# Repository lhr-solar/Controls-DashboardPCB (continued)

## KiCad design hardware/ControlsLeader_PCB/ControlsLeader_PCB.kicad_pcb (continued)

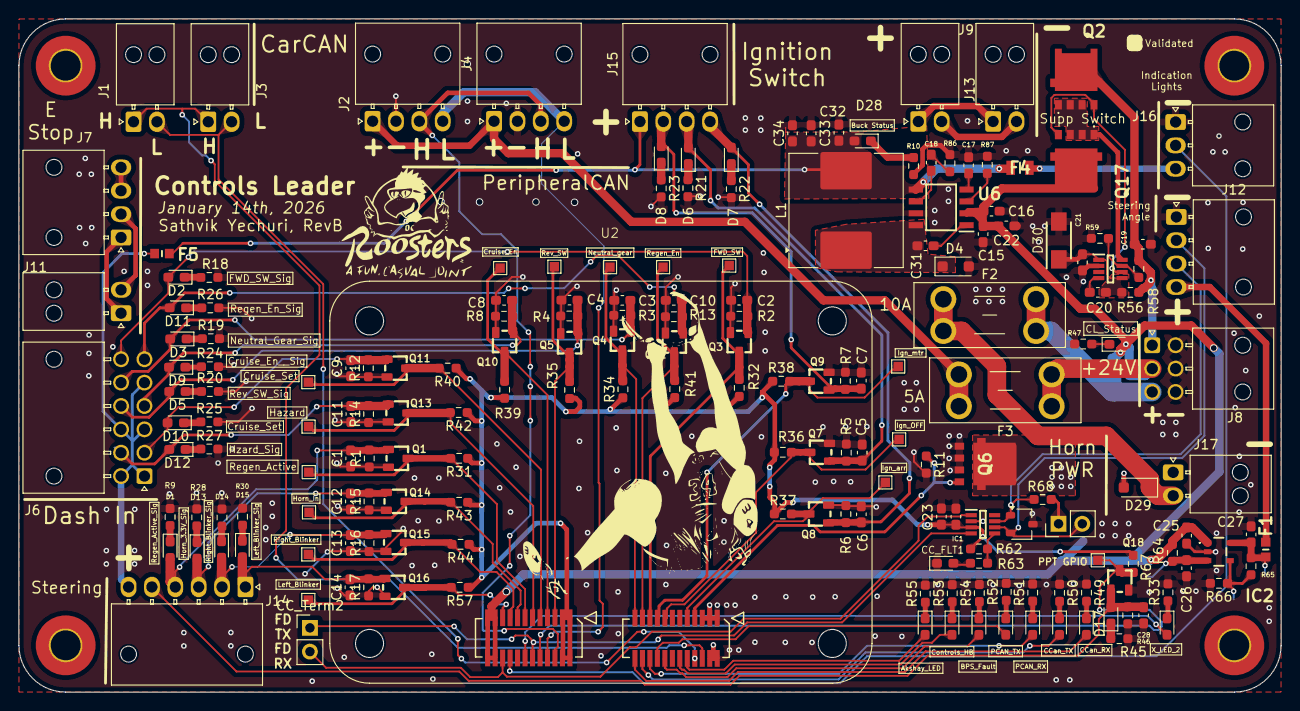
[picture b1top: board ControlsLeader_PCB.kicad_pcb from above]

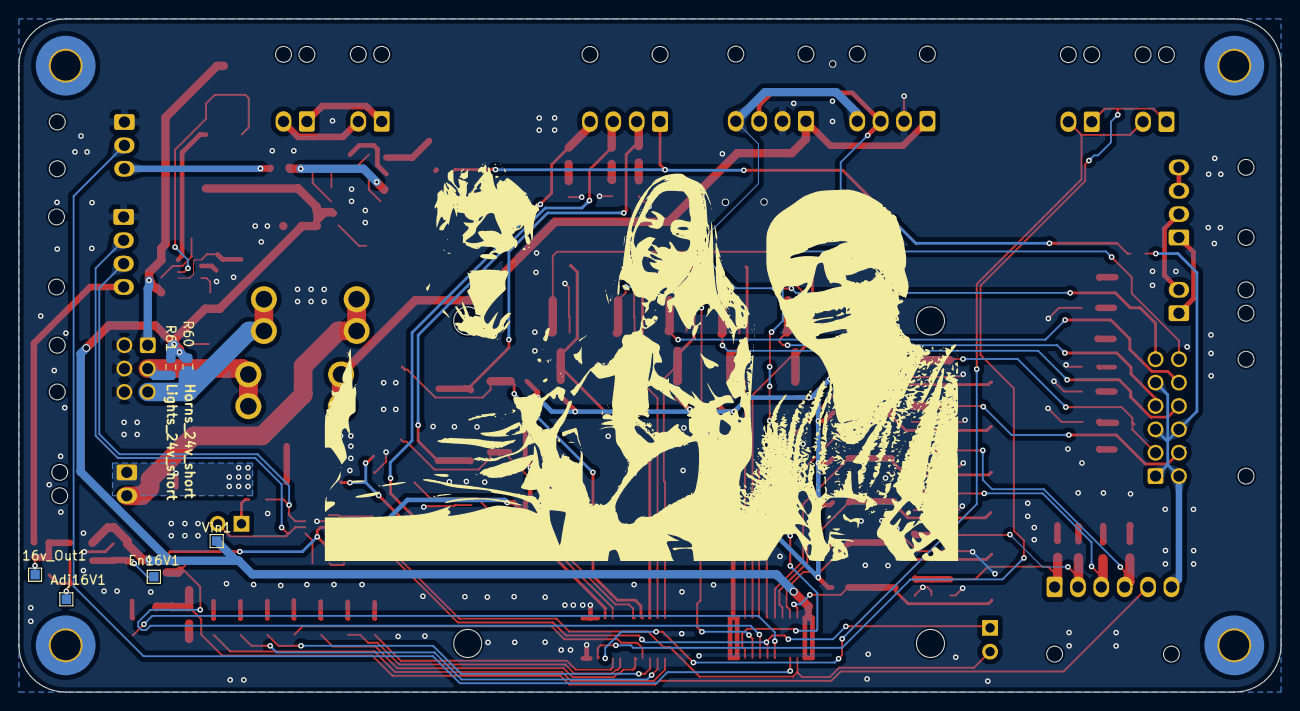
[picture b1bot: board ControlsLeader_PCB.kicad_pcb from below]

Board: 2 copper layers, 135.0 x 72.0 mm, 200 parts (6 on the bottom side), 108 nets.

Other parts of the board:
16v_Out1: 5V_Out; TestPoint_Pad_1.0x1.0mm
Adj16V1: Adj5V; TestPoint_Pad_1.0x1.0mm
C15, C32, C33, C34: 10uF; C_0603_1608Metric_Pad1.08x0.95mm_HandSolder
C16: 1uF; C_0603_1608Metric_Pad1.08x0.95mm_HandSolder
C17: 10nF; C_0603_1608Metric_Pad1.08x0.95mm_HandSolder
C18: 3.3nF; C_0603_1608Metric_Pad1.08x0.95mm_HandSolder
C31: 0.1uF; C_0603_1608Metric_Pad1.08x0.95mm_HandSolder
D4: MBR230S1F; D_SOD-123F
En16V1: Enable5V; TestPoint_Pad_1.0x1.0mm
L1: 100uH; L_Coilcraft_MSS1246-XXX
R86: 16k; R_0603_1608Metric_Pad0.98x0.95mm_HandSolder
R87: ROSC; R_0603_1608Metric_Pad0.98x0.95mm_HandSolder
U6: TPS5405DR

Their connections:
+24V: C15.1, C16.1, U6.2 (VIN); also elsewhere on the board
/5V_Buck: C32.1, C33.1, C34.1, L1.2, U6.5 (VSENSE); also elsewhere on the board
/24v_5v_Buck/LX: C31.2, D4.1 (K), L1.1, U6.8 (LX)
/24v_5v_Buck/ROSC: R87.1, U6.3 (ROSC)
/Steering Angle Sensor Components/24v to 16v ldo/16v_prefuse: 16v_Out1.1; also elsewhere on the board
GND: C15.2, C16.2, C17.2, C32.2, C33.2, C34.2, D4.2 (A), R86.2, R87.2, U6.7 (GND); also elsewhere on the board
unnamed: C18.2, R86.1
unnamed 100: Adj16V1.1; also elsewhere on the board
unnamed 101: En16V1.1; also elsewhere on the board
unnamed: C31.1, U6.1 (BOOT)
unnamed: C18.1, U6.6 (COMP)
unnamed: C17.1, U6.4 (SS)

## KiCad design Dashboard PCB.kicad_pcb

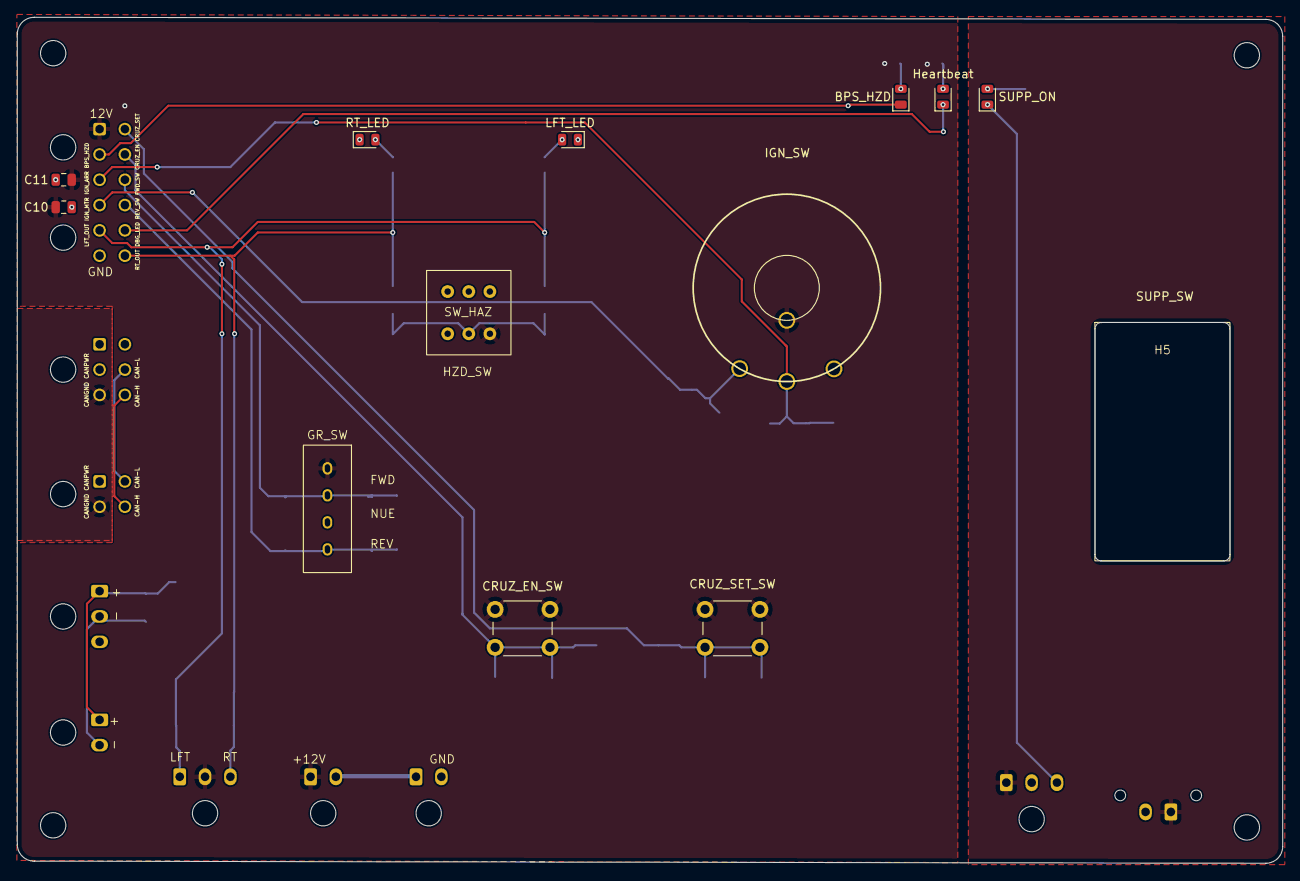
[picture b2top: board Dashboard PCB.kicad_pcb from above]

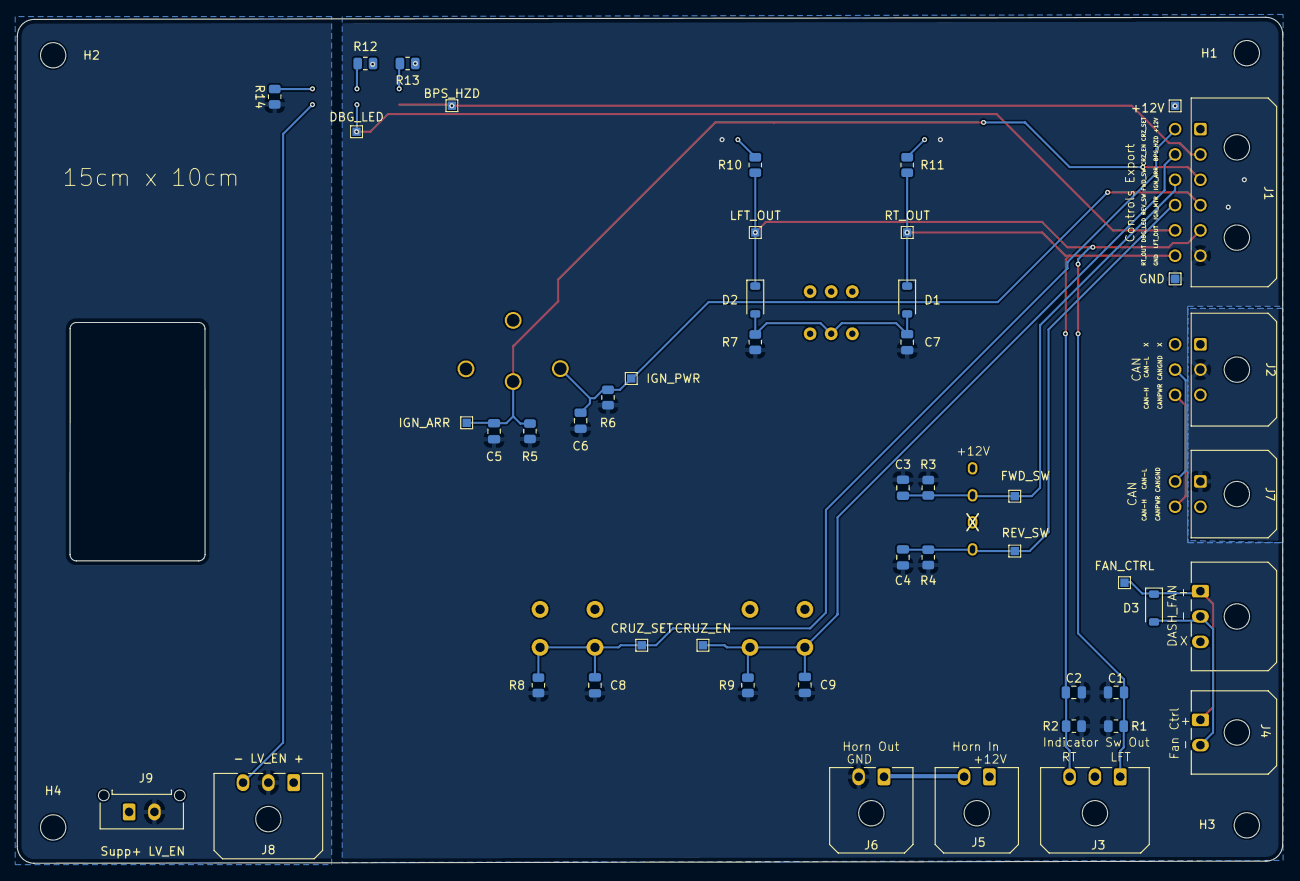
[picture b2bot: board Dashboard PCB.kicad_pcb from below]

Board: 2 copper layers, 150.0 x 100.2 mm, 66 parts (49 on the bottom side), 28 nets.

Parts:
+12V: TestPoint; TestPoint_Pad_1.0x1.0mm
BPS_HZD: SMD_0805_RED; LED_0805_2012Metric
BPS_HZD#2: TestPoint; TestPoint_Pad_1.0x1.0mm
C1, C2, C3, C4, C5, C6, C7, C8, C9: 5uF; C_0805_2012Metric
C10, C11: 100uF; C_0805_2012Metric
CRUZ_EN: TestPoint; TestPoint_Pad_1.0x1.0mm
CRUZ_EN_SW: CRUSE_EN_SW_12V; SW_PUSH_6mm
CRUZ_SET: TestPoint; TestPoint_Pad_1.0x1.0mm
CRUZ_SET_SW: CRUSE_SET_SW_12V; SW_PUSH_6mm
D1, D2: BAV16W; D_SOD-123
D3: 1N5819HW; D_SOD-123
DASH_FAN1: DASHBOARD_FAN_12V; Molex_Micro-Fit_3.0_43650-0300_1x03_P3.00mm_Horizontal
DBG_LED: TestPoint; TestPoint_Pad_1.0x1.0mm
FAN_CTRL: TestPoint; TestPoint_Pad_1.0x1.0mm
FWD_SW: TestPoint; TestPoint_Pad_1.0x1.0mm
GND: TestPoint; TestPoint_Pad_1.0x1.0mm
GR_SW: GEAR_SW_12V; 3posSlideToggle
H1, H2, H3, H4: MountingHole; MountingHole_3mm
H5: SuppSwitchMount; Supp_Switch
HZD_SW: HAZARD_SWITCH_12V; Toggle
Heartbeat: SMD_0805_GRN; LED_0805_2012Metric
IGN_ARR: TestPoint; TestPoint_Pad_1.0x1.0mm
IGN_PWR: TestPoint; TestPoint_Pad_1.0x1.0mm
IGN_SW1: IGNITION_SW_12V; SW_3POS_ROT
J1: Controls_Leader_Export_02x06; Molex_Micro-Fit_3.0_43045-1200_2x06_P3.00mm_Horizontal
J2: Conn_02x03_CAN; Molex_Micro-Fit_3.0_43045-0600_2x03_P3.00mm_Horizontal
J3: INDICATOR_SWITCH_OUT; Molex_Micro-Fit_3.0_43650-0300_1x03_P3.00mm_Horizontal
J4: FAN_CTRL_01x02; Molex_Micro-Fit_3.0_43650-0200_1x02_P3.00mm_Horizontal
J5: Horn_In_01x02; Molex_Micro-Fit_3.0_43650-0200_1x02_P3.00mm_Horizontal
J6: Horn_Out_01x02; Molex_Micro-Fit_3.0_43650-0200_1x02_P3.00mm_Horizontal
J7: Conn_02x03_CAN; Molex_Micro-Fit_3.0_43045-0400_2x02_P3.00mm_Horizontal
J8: Supp_Out; Molex_Micro-Fit_3.0_43650-0300_1x03_P3.00mm_Horizontal
J9: Supp_In; Molex_Micro-Fit_3.0_43650-0215_1x02_P3.00mm_Vertical
LFT_LED: SMD_0805; LED_0805_2012Metric
LFT_OUT: TestPoint; TestPoint_Pad_1.0x1.0mm
R1, R2, R3, R4, R5, R6, R7, R8, R9: 10k; R_0805_2012Metric
R10, R11, R12, R14: 5.1k; R_0805_2012Metric
R13: HZD_RES_VAL; R_0805_2012Metric
REV_SW: TestPoint; TestPoint_Pad_1.0x1.0mm
RT_LED: SMD_0805; LED_0805_2012Metric
RT_OUT: TestPoint; TestPoint_Pad_1.0x1.0mm
SUPP_ON: LED; LED_0805_2012Metric

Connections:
+12V: +12V.1, C10.1, C11.1, CRUZ_EN_SW.1, CRUZ_SET_SW.1, GR_SW.1, HZD_SW.1, IGN_SW1.1, J1.1, J3.2, J5.1, R12.1, R13.1
/BPS_HZD: BPS_HZD.1 (K), BPS_HZD#2.1, J1.2
/CAN+12V: J2.3, J7.2
/CAN-H: J2.6, J7.4
/CAN-L: J2.5, J7.3
/CANGND: J2.2, J7.1
/CRUZ_EN: C9.1, CRUZ_EN.1, CRUZ_EN_SW.2, J1.8, R9.2
/CRUZ_SET: C8.1, CRUZ_SET.1, CRUZ_SET_SW.2, J1.7, R8.1
/DBG_LED: DBG_LED.1, Heartbeat.1 (K), J1.11
/FAN+: D3.1 (K), DASH_FAN1.1, FAN_CTRL.1, J4.1
/FAN-: D3.2 (A), DASH_FAN1.2, J4.2
/FWD_SW: C3.2, FWD_SW.1, GR_SW.2, J1.9, R3.2
/IGN_ARR: C5.1, IGN_ARR.1, IGN_SW1.3, J1.3, R5.2
/IGN_MTR: C6.1, IGN_PWR.1, IGN_SW1.2, J1.4, R6.2
/LFT_OUT: C1.2, D2.1 (K), J1.5, J3.1, LFT_OUT.1, R1.1, R10.1
/LV_EN: J8.2, J9.2, R14.1
/REV_SW: C4.1, GR_SW.4, J1.10, R4.1, REV_SW.1
/RT_OUT: C2.1, D1.1 (K), J1.12, J3.3, R2.2, R11.1, RT_OUT.1
/Supp+: J8.1, J9.1
/Supp-: J8.3, SUPP_ON.1 (K)
GND: C1.1, C2.2, C3.1, C4.2, C5.2, C6.2, C7.2, C8.2, C9.2, C10.2, C11.2, GND.1, J1.6, J6.2, LFT_LED.1 (K), R1.2, R2.1, R3.1, R4.2, R5.1, R6.1, R7.1, R8.2, R9.1, RT_LED.1 (K)
unnamed: BPS_HZD.2 (A), R13.2
unnamed: C7.1, D1.2 (A), D2.2 (A), HZD_SW.2, R7.2
unnamed: R14.2, SUPP_ON.2 (A)
unnamed: Heartbeat.2 (A), R12.2
unnamed: J5.2, J6.1
unnamed: LFT_LED.2 (A), R10.2
unnamed: R11.2, RT_LED.2 (A)

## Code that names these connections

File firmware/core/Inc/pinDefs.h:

#pragma once

#include "stm32xx_hal.h"

/* -------- Output LEDs - CAN -------- */
#define PH_CAN_RX_LED_PORT      GPIOA
#define PH_CAN_RX_LED_PIN       GPIO_PIN_10
#define CAR_CAN_RX_LED_PORT     GPIOB
#define CAR_CAN_RX_LED_PIN      GPIO_PIN_3
#define CAR_CAN_TX_LED_PORT     GPIOB
#define CAR_CAN_TX_LED_PIN      GPIO_PIN_5
#define PH_CAN_TX_LED_PORT      GPIOB
#define PH_CAN_TX_LED_PIN       GPIO_PIN_4

/* -------- Output LEDs - Status -------- */
#define INDICATION_PWN_PORT 	GPIOB
#define INDICATION_PWM_PIN		GPIO_PIN15
#define X_LED2_PORT             GPIOB
#define X_LED2_PIN              GPIO_PIN_14
#define CONTROLS_HB_LED_PORT    GPIOB
#define CONTROLS_HB_LED_PIN     GPIO_PIN_10
#define AKSHAY_LED_PORT         GPIOB
#define AKSHAY_LED_PIN          GPIO_PIN_11
#define BPS_FAULT_LED_PORT      GPIOC
#define BPS_FAULT_LED_PIN       GPIO_PIN_1
#define LSOM_HB_PORT            GPIOC
#define LSOM_HB_PIN             GPIO_PIN_3

/* -------- Output - GPIO -------- */
#define HORN_OUT_PORT           GPIOB
#define HORN_OUT_PIN            GPIO_PIN_1

/* -------- Input - Ignition -------- */
#define IGN_OFF_PORT            GPIOA
#define IGN_OFF_PIN             GPIO_PIN_2
#define IGN_MTR_PORT            GPIOA
#define IGN_MTR_PIN             GPIO_PIN_1
#define IGN_ARR_PORT            GPIOB
#define IGN_ARR_PIN             GPIO_PIN_0

/* -------- Input - Switches -------- */
#define FWD_SW_PORT             GPIOA
#define FWD_SW_PIN              GPIO_PIN_0
#define REV_SW_PORT             GPIOC
#define REV_SW_PIN              GPIO_PIN_7
#define NEUTRAL_GEAR_PORT       GPIOC
#define NEUTRAL_GEAR_PIN        GPIO_PIN_0
#define PTT_PORT                GPIOB
#define PTT_PIN                 GPIO_PIN_2
#define HORN_PORT               GPIOD
#define HORN_PIN                GPIO_PIN_2

/* -------- Input - Cruise -------- */
#define CRUISE_ENABLE_PORT      GPIOC
#define CRUISE_ENABLE_PIN       GPIO_PIN_6
#define CRUISE_SET_PORT         GPIOC
#define CRUISE_SET_PIN          GPIO_PIN_9

/* -------- Input - Regen -------- */
#define REGEN_ENABLE_PORT       GPIOC
#define REGEN_ENABLE_PIN        GPIO_PIN_2
#define REGEN_ACTIVE_PORT       GPIOC
#define REGEN_ACTIVE_PIN        GPIO_PIN_12

/* -------- Input - Blinkers -------- */
#define RIGHT_BLINKER_PORT      GPIOC
#define RIGHT_BLINKER_PIN       GPIO_PIN_4
#define LEFT_BLINKER_PORT       GPIOC
#define LEFT_BLINKER_PIN        GPIO_PIN_5
#define HAZARD_PORT             GPIOC
#define HAZARD_PIN              GPIO_PIN_8


/* -------- Output - GPIO -------- */
#define CAR_CAN_TX_PORT			GPIOA
#define CAR_CAN_TX_PIN			GPIO_PIN_15

#define CAR_CAN_RX_PORT			GPIOA
#define CAR_CAN_RX_PIN			GPIO_PIN_8

#define LIGHTING_CAN_TX_PORT	GPIOA
#define LIGHTING_CAN_TX_PIN		GPIO_PIN_12

#define LIGHTING_CAN_RX_PORT	GPIOA
#define LIGHTING_CAN_RX_PIN		GPIO_PIN_11



/* -------- Output - UART printf -------- */
#define USART3_PORT				GPIOC
#define USART3_TX_PIN			GPIO_PIN_10
#define USART3_RX_PIN			GPIO_PIN_11

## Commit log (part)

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2024-10-08 Dashboard PCB :anguished:
2024-10-12 Ready for review I think :+1:
    Switched design from modular to big board :). Plz rev schem thaks :P
2024-10-12 Hotfix
    Changed ignition switch to not have ON, and added supp pwr switch
2024-10-12 Added dashboard fan connection
    Not sure if i need to do anything specific with the fan (flyback diode?)
2024-10-12 Updated dashboard
    Took off some unnecessary connections
2024-10-12 Major redisign
    Added a lot of stuff and redesigned a lot of stuff
2024-10-12 ddelet img
2024-10-18 Update 1/2
    Fixed some of the requested changes.
    Still need to fix it up a bit more.
2024-10-19 Ready for review
    Controls decided to move a bunch of stuff back to leaderboard, also I think I fixed everything else.
2024-10-25 Made pretty
    Fixed a few things up and made it pretty.
    Still need to double check a few things and assign all footprints
2024-10-26 Started assigning footprints
    Still have a few missing, and not sure if im doing it all right
2024-10-26 Added excel sheet
2024-11-02 Added a lot footprints
    Some of them are custom and need to be double checked. Also no sure if they are all correctly included
2024-11-02 Added footprints locally
2024-11-02 Footprint all assigned, and updated to PCB
    Ready for a check in to make sure everything is looking alright
2024-11-09 Fixed fan and rot switch
2024-11-09 Preliminary PCB layout
2024-11-09 Preliminary schematic
2024-11-09 r pt 2
2024-11-23 Changed layout, added 3d models
2024-11-24 Some extra stuff and things
2024-11-24 Fixed stuff
2024-11-24 Routing finished :0
2024-12-02 Routed
2024-12-05 changed routing
2024-12-05 More stuff
2024-12-06 Filter move >:(
2024-12-07 Changed size and rerouted
2024-12-07 Labled n other stuff
2024-12-07 A bunch of stuff
2024-12-14 Supp changes
2025-01-16 Final changes for now
    added p/n n stuff
2025-01-16 Added gerbers
2025-02-01 helow
2025-02-22 Shenanigans
2025-02-26 Schematic updates. Ready for review, I think.
2025-02-26 Changed from Internal CAN to Peripheral CAN
2025-03-05 Dashboard PCB :anguished: (#1)
    * Dashboard PCB :anguished:
    * Ready for review I think :+1:
    Switched design from modular to big board :). Plz rev schem thaks :P
    * Hotfix
    Changed ignition switch to not have ON, and added supp pwr switch
    * Added dashboard fan connection
2025-12-27 ShaqDash is born. . . RPP in progress
2025-12-28 Rev B :)
2026-01-10 Rev B Layout
2026-01-10 i hate git
2026-01-10 i beg of git
2026-01-14 Steering Angle Sensor SCH changes
2026-01-15 revb layout, working on silkscreen
2026-01-15 RevB done :)
2026-01-15 Rev B Gerbers and JLCpcb stuff :)
2026-01-15 Final fixes
2026-01-15 gerber and jlc files
2026-01-15 updated jlc parts list
2026-01-16 cleaning up files
2026-01-17 RevB 'Merge'
2026-01-17 RevB 'Merge' (#9)
2026-01-17 Nucleo Test init
2026-01-17 Test files init
2026-01-17 ready for nucleo testing, waiting on nucelo :(
2026-01-23 Add README.md for Controls Leader documentation
    Added detailed documentation for the Controls Leader board, including hardware architecture, input interfaces, and repository structure.
2026-01-23 gitignore
2026-01-23 code shenanigins
2026-01-23 Mika is quite smart
2026-01-23 Mika is quite smart (#12)
2026-01-23 i ahte fixing git
2026-01-23 firmware init 2.0
2026-01-25 IO testing
2026-01-26 IO test 1.1
2026-01-26 IO TEST WORKSSS
2026-01-26 ew build, only mika would keep ts
2026-01-29 .h files done
2026-01-31 TODO: software design ip
2026-02-02 github actions and flash-uart code
2026-02-06 RTOS Structure done, need to write actuaul functions (currently have blinky which tweaks)
2026-02-13 gpio interruptss in progress
2026-04-01 Rev b (#8)
    * Branch Init
    * Schematic done, GPIO on .ioc TBD
    * Board review
    * Fixing kicad sharepoint
    * Reinit KiCAD Sharepoint
    * Schematic Backup
2026-04-03 PLEASEEEE CHUDSHAYYY
2026-04-03 breh
2026-04-03 remove orphaned submodule hardware/ControlsLeader_PCB/lib/KiCAD-Sharepoint
2026-04-03 re adding embedded share p
2026-04-03 aarav chud
2026-04-03 mehhhhhhhhhhhhhhhhhhhhhhhhhhhhhhhhhhhhhhhhhhhhhhhhhhh
2026-04-03 i'm stupid
2026-04-03 bahhhh
2026-04-03 im dum
2026-04-03 BROOOOOOOOOOOOOOOOOOOOOOOOOOO
2026-04-03 im very very dum
2026-04-03 hmmmmmmmmmmm
2026-04-04 MERGEEEEEEEEEEEEEEEEEEEEEEEEEEEEEEE
2026-04-04 MERGEEEEEE 6.7
2026-04-04 breh 6.7
2026-04-04 PLSSSS MERGEEEE
2026-04-05 AHHHHHHHHHHHHH
2026-04-05 bruh
2026-04-05 grhhhh
2026-04-05 finally please everything workssssssssss
2026-04-05 doneeeeee
2026-04-05 BRUHHHHHHHHHHHHHHHHHHHHHHHHHHHHHHHHHHHHHHHHHHHHHHHHHHHHHHHHHHHHHHHHHHHHHHHHHHHHHHHHHHHHHHHHHHHHHHHHHHHHHHHHHHHHHHHHHHHHHHHH now its done
2026-04-05 Dash Drivers (#14)
    * firmware init 2.0
    * IO testing
    * Delete firmware/.venv directory
    * IO test 1.1
    * IO TEST WORKSSS
    * ew build, only mika would keep ts
2026-04-07 CANNNFD WORKKKKKKKKSSSSSSSSSSSSSSSSSSSSSSSSSSSSSSSSSSSSSSSSSSSSSSSSSSSSSSSSSSSSSSS
2026-04-11 ready for testing ign + can
2026-04-11 bnruh
2026-04-11 woooooooooooooooooooooooooo
2026-04-11 ign wokrssss
2026-04-11 lakslay
2026-04-11 stuoopid build
2026-04-11 stoopid .vscode
2026-04-11 car can rx todo
2026-04-17 unveiling lighting can messages
2026-04-21 pwered run shi
2026-05-07 no jumpstart
2026-05-24 goofy ah embedded sharepoint lakhsy goon
2026-05-24 beuhhhhhhhhhhhhhhhhhhhhhhhh
2026-05-24 fixing build errors
2026-06-07 test
2026-06-20 steering done
2026-06-21 stoopid fix
2026-06-21 baahahhahah - horn
2026-06-28 remove da bs
2026-06-28 steering fw forwarding verified
